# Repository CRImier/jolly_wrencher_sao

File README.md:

# Jolly Wrencher SAO

This is a Jolly Wrencher SAO, loosely adherent to [SAO v1.69bis](https://hackaday.com/2019/03/20/introducing-the-shitty-add-on-v1-69bis-standard/).

It accepts both SMD and through-hole 2.54mm (0.1") pitch connectors.
For the Supercon 2022 badge, you will want to populate at least the "main" section
(marked on the silkscreen) - extra pins will be handy if you want to use this SAO
with some of the 6-pin connector badges.

On the back, it has as much prototyping space as I could fit in there, on a 1.27mm (0.05") grid,
non-connected pads diagonally interspersed with GND pads for easier prototyping.
There's no through-holes because I didn't want to ruin the front of the badge.
You should be able to fit an ESP32 SMD module on there, for instance - I haven't considered this usecase
specifically, but I think its pins are on 1.27mm grid?

There's also 0805 footprints for LEDs behind the eyes, with the eyes themselves
being transparent - mask, silk and copper removed. I hope it's not going to look awful.
The 0805 footprints, being "handsoldering" and wider, should be 0603-compatible.
I also wish you personally that the eye portion of the FR4 on your badge won't bear any
marks that are often put on the surface of bare (exposed) FR4.
One side of these LEDs is connected to VCC, the other, you'll want to connect to GND
with some resistor - there's no extra resistor footprint, but GND pads are very much nearby!

There's a `^^` version in this repository, which has `^ ^` instead of the usual Wrencher eyes.
That's the only difference. I'm making that one for myself and my friends, you order whatever.
The `svgs/` folder contains source SVGs and some random in-progress stuff, didn't want to clean it up.

Hackaday, Hack A Day, and the Skull and Wrenches Logo are Trademarks of Hackaday.com.

If you're ordering from JLCPCB and they send you an email saying that they'd like you
to upgrade to ENIG, see [JLCPCB_SPEECH_CHECK.md](./JLCPCB_SPEECH_CHECK.md).
Of course, you can also upgrade to ENIG, I'm not your mom or something.

- Signal names are silkscreened on the board's bottom layers.
- This board is untested and there's no guarantees of fitness.

- Software: Kicad 6
- Version: 2 (I published v1 on Discord somewhere, who knows if it got ordered by someone, warrants a bump)
- PCB size: 47.93mm*43.85mm  (JLCPCB said so, idk how to properly measure an arbitrary shape PCB in KiCad)
- Layer count: 2
- Recommended thickness: whatever, maybe not 0.8mm? I ordered 1.2mm IIRC
- Recommended silkscreen color: black

## Credits

The wrencher SVG design is from https://github.com/n1/Wrencher-Display - thanks to @n1 for sharing it!

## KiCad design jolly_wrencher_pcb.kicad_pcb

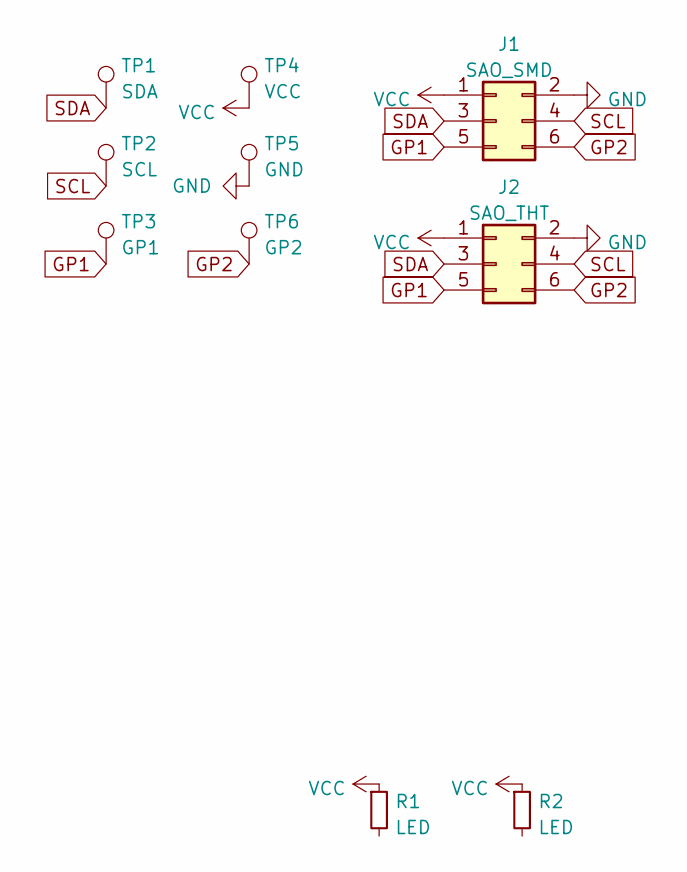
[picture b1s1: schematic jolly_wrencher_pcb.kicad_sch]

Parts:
J1: SAO_SMD; PinHeader_2x03_P2.54mm_Vertical_SMD
J2: SAO_THT; IDC-Header_2x03_P2.54mm_Vertical
R1, R2: LED; R_0805_2012Metric_Pad1.20x1.40mm_HandSolder
TP1: SDA; TestPoint_Pad_D1.5mm
TP2: SCL; TestPoint_Pad_D1.5mm
TP3: GP1; TestPoint_Pad_D1.5mm
TP4: VCC; TestPoint_Pad_D1.5mm
TP5: GND; TestPoint_Pad_D1.5mm
TP6: GP2; TestPoint_Pad_D1.5mm

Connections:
GND: J1.2, J2.2, TP5.1
GP1: J1.5, J2.5, TP3.1
GP2: J1.6, J2.6, TP6.1
SCL: J1.4, J2.4, TP2.1
SDA: J1.3, J2.3, TP1.1
VCC: J1.1, J2.1, R1.1, R2.1, TP4.1

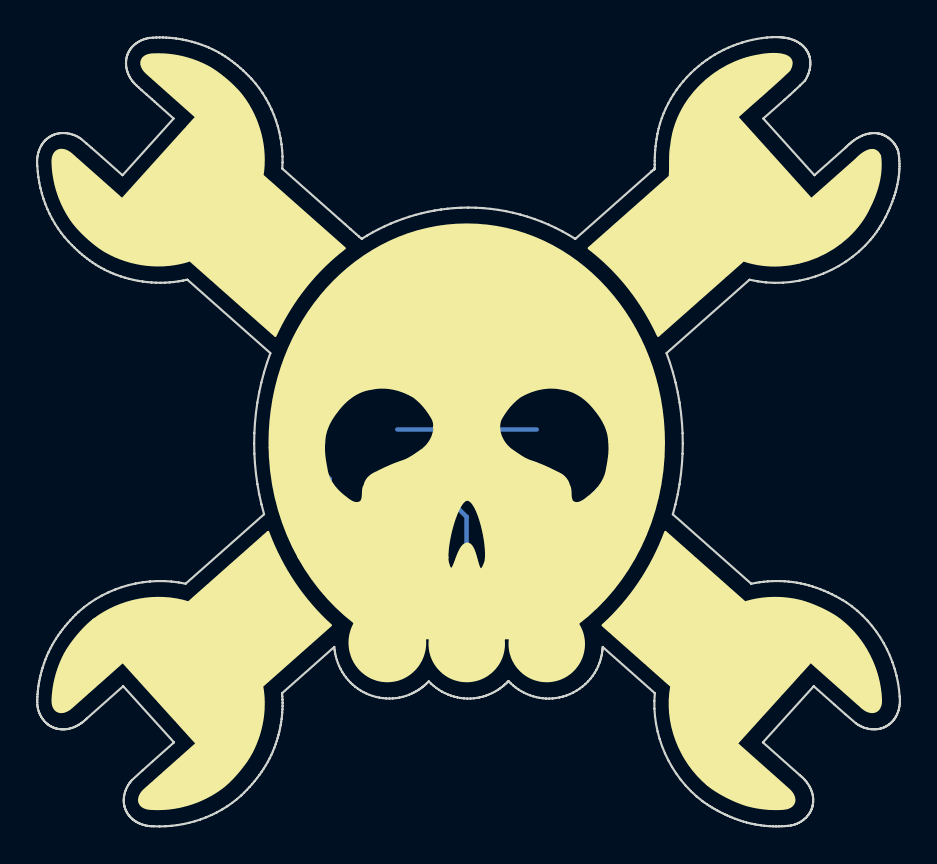
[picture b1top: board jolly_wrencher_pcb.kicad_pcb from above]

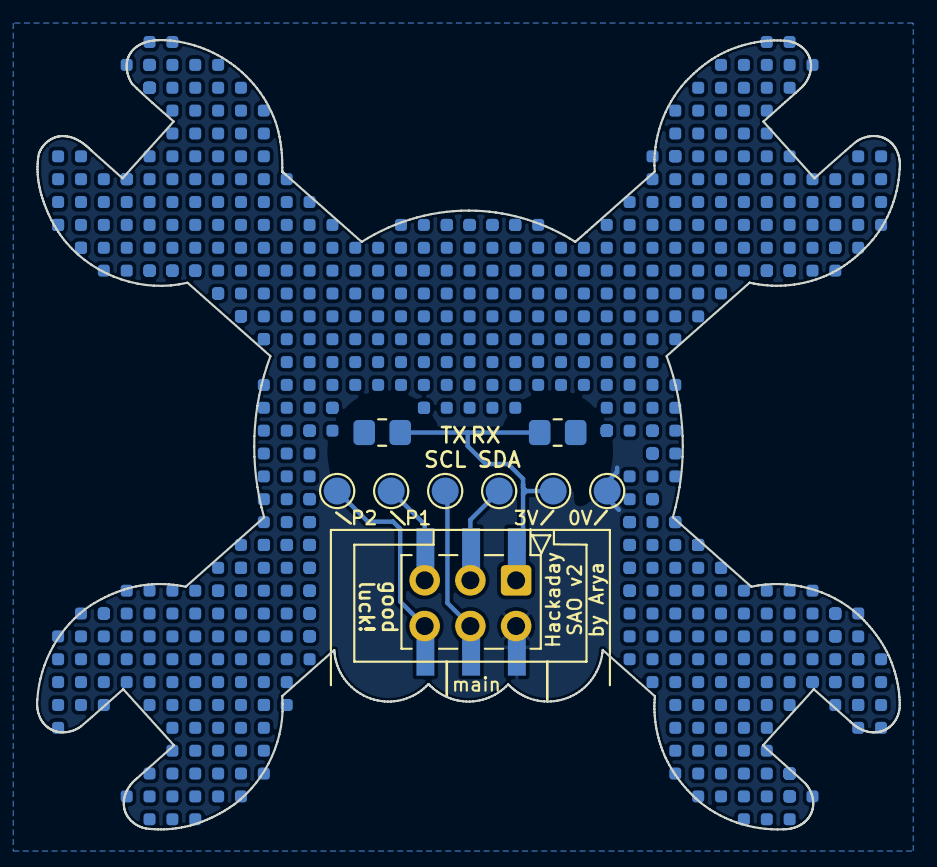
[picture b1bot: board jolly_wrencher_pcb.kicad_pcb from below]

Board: 2 copper layers, 47.9 x 43.9 mm, 10 parts (10 on the bottom side), 6 nets.
